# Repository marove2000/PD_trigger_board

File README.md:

# PD trigger board

## ToDo for v0.2
- ~~Stamp attachments~~
- ~~USBC smd-mounted with holes -> https://jlcpcb.com/partdetail/Dealon-USB_TYPE_C020/C2927040~~
- ~~Writing on board not visible~~
- ~~Version on board~~
- ~~Power-Output to right side~~
- ~~Delete current-table~~
- ~~If possible: Writing to top~~
- ~~Size like C3-Mini~~
- ~~If needed: Remove 18V~~
- One pin with 5V 300mA output (step down)
- Kompatiblität mit: https://wiki.seeedstudio.com/Seeeduino-XIAO/ (Adapterplatine)
- Kompatiblität mit: https://cdn.mikroe.com/cms/click-boards/click-board-standard-guidelines-april-2019.pdf (Über Adapterplatine)
- ~~FSCS zu LCSC ändern~~
- ~~Bigger Thruholes~~ 

## ToDo for future release
- Footprint for SMD attachment
- ~~Stackable Design~~
- PD 3.1? https://www.lcsc.com/product-detail/USB-PD_Hynetek-HUSB238A-BB001-QN16R_C24833806.html

## other boards

Adafruit: https://www.adafruit.com/product/5807
https://learn.adafruit.com/adafruit-husb238-usb-type-c-power-delivery-breakout/overview
Blog: https://blog.adafruit.com/2022/05/04/plug-n-play-usb-type-c-dummy-pd/
isaac: https://github.com/isaac879/USB-Type-C-PD-Trigger-Board?tab=readme-ov-file

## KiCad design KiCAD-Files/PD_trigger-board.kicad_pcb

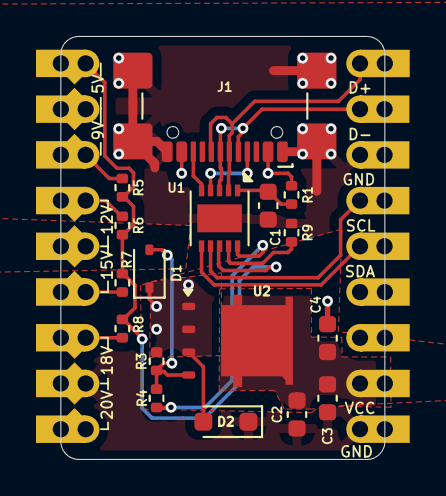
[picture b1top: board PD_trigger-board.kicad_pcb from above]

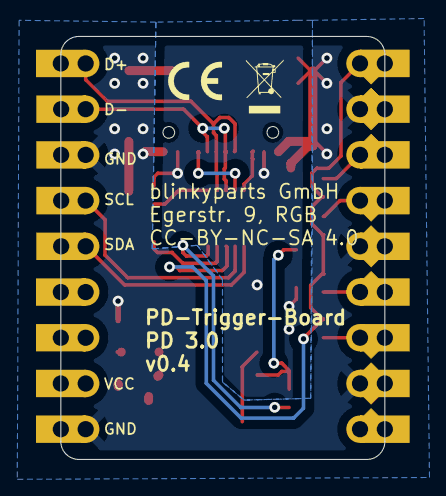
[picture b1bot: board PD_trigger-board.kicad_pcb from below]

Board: 2 copper layers, 18.0 x 23.5 mm, 20 parts (2 on the bottom side), 18 nets.

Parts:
C1: 1uF 50V; C_0603_1608Metric
C2, C3, C4: 4.7uF 35V; C_0603_1608Metric
D1: D_Zener; D_SOD-323
D2: SD15_SOD323; D_SOD-323_HandSoldering
J1: USB_C_Receptacle_USB3.0_12P; USB_C_Receptacle_GCT_USB4110
R1: 10R; R_0402_1005Metric
R3: 49.9k; R_0402_1005Metric
R4: 5.1k; R_0402_1005Metric
R5: 6.04k; R_0402_1005Metric
R6: 10k; R_0402_1005Metric
R7: 14k; R_0402_1005Metric
R8: 18k; R_0402_1005Metric
R9: 22.6k; R_0402_1005Metric
U1: HUSB238; DFN-10-1EP_3x3mm_P0.5mm_EP1.55x2.48mm
U2: SIR1309DP; PowerPAK_SO-8L_Single
U3: ESP32-S3-mini_pinprofile; ESP32-S3-Zero
ce_icon_SilkS_3mm: G***; ce-icon_SilkS_3mm
weee-icon_SilkS_3mm: G***; weee-icon_SilkS_3mm

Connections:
CC1: J1.A5 (CC1), U1.4 (CC1)
CC2: J1.B5 (CC2), U1.5 (CC2)
D+: J1.A6 (D+), J1.B6 (D+), U1.2 (D+), U3.18 (D+)
D-: J1.A7 (D-), J1.B7 (D-), U1.3 (D-), U3.17 (D-)
GATE: R4.2, U1.10 (GATE)
GND: C1.2, C2.2, C3.2, C4.2, D2.1 (A1), J1.A1 (GND), J1.A12 (GND), J1.B1 (GND), J1.B12 (GND), J1.S1 (SHIELD), R9.2, U1.11 (GND), U3.2 (GND), U3.5 (GND), U3.8 (GND), U3.10 (GND), U3.16 (GND)
unnamed: D1.2 (A), R3.2, R4.1, U2.4 (G)
unnamed: R9.1, U1.9 (ISET)
unnamed: C1.1, R1.2, U1.1 (VIN)
unnamed: R5.2, U3.3 (SET_9V)
unnamed: R6.2, U3.4 (SET_12V)
unnamed: R7.2, U3.6 (SET_15V)
unnamed: R8.2, U3.7 (SET_18V)
SCL: U1.7 (SCL), U3.15 (SCL)
SDA: U1.6 (SDA), U3.14 (SDA)
VBUS: D1.1 (K), D2.2 (A2), J1.A4 (VBUS), J1.A9 (VBUS), J1.B4 (VBUS), J1.B9 (VBUS), R1.1, R3.1, U2.1 (S), U2.2 (S), U2.3 (S)
VOUT: C2.1, C3.1, C4.1, U2.5 (D), U3.11 (VOUT)
VSET: R5.1, R6.1, R7.1, R8.1, U1.8 (VSET), U3.1 (SET_5V)

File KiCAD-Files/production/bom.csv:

Designator,Footprint,Quantity,Value,LCSC Part #
C1,0603,1,1uF 50V,C15849
"C2, C3, C4",0603,3,4.7uF 35V,C307467
D1,D_SOD-323,1,D_Zener,C19077451
D2,D_SOD-323_HandSoldering,1,SD15_SOD323,C5253553
J1,USB_C_Receptacle_GCT_USB4110,1,USB_C_Receptacle_USB3.0_12P,C136423
R1,0402,1,10R,C25139
R3,0402,1,49.9k,C100457
R4,0402,1,5.1k,C25941
R5,0402,1,6.04k,C25913
R6,0402,1,10k,C25531
R7,0402,1,14k,C54831
R8,0402,1,18k,C25542
R9,0402,1,22.6k,C54831
U1,DFN-10-1EP_3x3mm_P0.5mm_EP1.55x2.48mm,1,HUSB238,C7471904
U2,PowerPAK_SO-8L_Single,1,SIR1309DP,C5919282
U3,ESP32-S3-Zero,1,ESP32-S3-mini_pinprofile,

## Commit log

2024-11-07 inital commit with the rough schematics
2024-11-07 added gitignore
2024-11-08 added readme
2024-11-08 added some data sheets
2024-11-10 start routing
2024-11-23 Routin fertig
2024-11-23 Routing fertig
2024-11-25 changed some routing
2024-11-25 Silkscreen fertig
2024-11-25 Silkscreen update
2024-11-25 added gerber files and made minor modifications
2024-11-26 Partlist fertig
2024-11-26 .BOM File erstellt
2025-01-04 added video for soldering
2025-01-04 minor changes for v0.1
2025-01-04 added notes for v0.2
2025-01-05 added some more notes
2025-01-05 added documents for ESP32-layout
2025-01-05 added footprint for S3-mini
2025-01-05 first draft of new layout
2025-01-07 Layout completed, ToDo processed
2025-01-08 smaller changes
2025-01-08 Minor design changes
2025-01-08 added ce, weee and rohs symbols. Updated ESP32 footprint
2025-01-08 created gerber files for v0.2
2025-01-08 deleted temp files
2025-01-08 minor changes for v0.2
2025-01-20 README updated
2025-01-20 .gitignore updated
2025-01-20 Thruholes enlarged and aligned
2025-01-20 Silkscreen improvement
2025-01-20 Partdescription updated
2025-01-24 minor Silkscreenchanges
2025-01-24 iBOM erstellt
2025-02-06 MOSFET changed to SIR1309DP
2025-02-06 minor changes
2025-02-06 small Footprint changes
2025-02-06 thermal relief deleted
2025-02-11 changed version number. added ce and weee symbol
2025-03-06 Added Kicad Addon
2025-03-06 Add a THT Footprint
2025-03-06 Fix some Small Footprint Issues
2025-03-06 Add 3D Modells to Library
2026-01-06 added zener and tvs diode
2026-01-17 placed diodes and minor design changes

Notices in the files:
KiCAD-Files/PD_trigger-board.kicad_pcb:
CC-BY-NC-SA 4.0
